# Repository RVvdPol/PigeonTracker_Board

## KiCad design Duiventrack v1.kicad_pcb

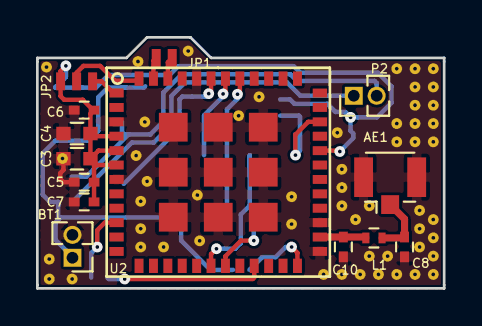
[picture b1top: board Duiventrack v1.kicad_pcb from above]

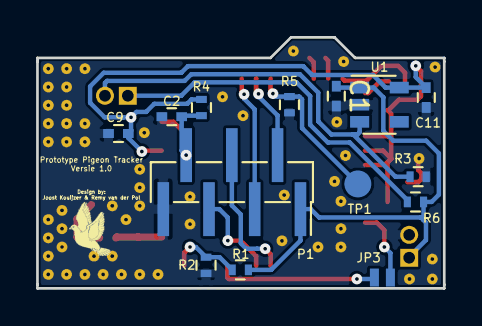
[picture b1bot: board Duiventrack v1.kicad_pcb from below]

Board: 2 copper layers, 22.6 x 13.9 mm, 28 parts (14 on the bottom side), 20 nets.

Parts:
AE1: Antenna_Shield; U.FL_Hirose_U.FL-R-SMT-1_Vertical
BT1: LiPo_Cell; Pin_Header_Straight_1x02_Pitch1.27mm
C1, C2, C6, C7: 100nF; C_0402
C3, C4: 10uF; C_0603
C5, C9, C11: 1uF; C_0402
C8, C10: F; C_0402
JP1, JP3: Jumper_NO_Small; SolderJumper_NO
JP2: Jumper_NC_Dual; SolderJumper_NO-3
L1: L; L_0402
P1: CONN_01X07; Pin_Header_Straight_1x07_Pitch1.27mm_SMD_Pin1Right
P2: CONN_01X02; Pin_Header_Straight_1x02_Pitch1.27mm
R1, R2: 10M; R_0402
R3: 1M; R_0402
R4, R5: 10K; R_0402
R6: 100K; R_0402
TP1: TEST; Measurement_Point_Round-SMD-Pad_Small
U1: MCP1711-SOT23-5; SOT-23-5
U2: SP-ABZ-G; Murata_SP-ABZ-G

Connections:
+3V3: C3.1, C4.1, C5.1, C6.1, C7.1, C9.1, C11.1, JP2.1, R4.1, U1.5, U2.4, U2.5, U2.6, U2.32
Earth: AE1.2, BT1.2, C1.2, C2.2, C3.2, C4.2, C5.2, C6.2, C7.2, C8.2, C9.2, C10.2, C11.2, P1.7, R2.2, R3.1, R5.2, U1.2, U2.3, U2.7, U2.25, U2.27, U2.44, U2.49, U2.50, U2.51, U2.52, U2.53, U2.54, U2.55, U2.56, U2.57
MCU_RST: C2.1, P1.6, R4.2, U2.34
unnamed: AE1.1, C8.1, L1.2
unnamed: C10.1, L1.1, U2.26
unnamed: JP1.1, U2.47
unnamed: JP1.2, U2.46
unnamed: JP2.2, U2.48
unnamed: JP2.3, U2.1
unnamed: JP3.1, U2.10
unnamed: JP3.2, U2.21
unnamed: P2.1, R6.1
unnamed: P2.2, R3.2, U1.3
unnamed: R5.1, TP1.1, U2.43
SWCLK: P1.2, U2.42
SWDIO: P1.3, U2.41
Uart_RX: P1.4, U2.18
Uart_TX: P1.5, U2.19
VBat: BT1.1, C1.1, P1.1, R1.1, R6.2, U1.1
VBat_Measure: R1.2, R2.1, U2.24

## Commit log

2018-04-25 Versie1
    eerste
2018-04-25 Component
    test
2018-04-25 test
    test
2018-04-25 Add component library
2018-04-25 Clean up missing libraries
2018-04-25 Add test point - boot-0 Connect VCC_TCX0 to VCC
2018-04-25 Testcommit remy
2018-04-25 Tescommit Joost
2018-04-25 Revert "Add test point - boot-0"
    This reverts commit 833b218a88f86450883f1825dc2b70f2262aafe3.
2018-04-25 Revert to working version Add test point
2018-04-25 Test werking
2018-04-25 Nieuwe versie, nadat het niet meer goed ging
2018-04-25 Foodprint testpunt toegevoegd, is alleen een beetje groot.
2018-05-01 Foutmelding murata component gaat nie weg
2018-05-01 Remove unavailable library's (murata lib)
2018-05-01 Schema afgemaakt en begonnen met de Footprint
2018-05-04 Aanpassingen gemaakt samen met Remy, board ontwerp
2018-05-04 Aanpassingen gemaakt aan het board, vooral de achterzijde, connector is anders aangesloten
2018-05-04 Overige aangesloten en fill zone toegevoegd, nog niet alles is geconnect, nog via nodig
2018-05-09 Vias toegevoegd voor ground
2018-05-09 Add connector 3d shape
2018-05-09 Add Murata LoRa 3d package
2018-05-09 Ground vias toegevoegd
2018-05-14 Crystal toegevoegd
2018-05-16 Revert "Crystal toegevoegd"
    This reverts commit 51f246dfdab6a70a9bd41b0f28c72966c573f5f4.
2018-05-16 drie solderjumpers toegevoegd, nog aan te sluiten
2018-05-18 Via en SolderJumper toegevoegd
2018-05-18 Small changes
2018-05-18 More small changes
2018-05-18 Add via's
2018-05-18 All connected and more vias
2018-05-18 Namen correct neer gezet en toegevoegd
2018-05-18 Decrease line clearance
2018-05-18 Duif toegevoegd
2018-05-18 Reduce line clearance
2018-05-25 Add 3d files
